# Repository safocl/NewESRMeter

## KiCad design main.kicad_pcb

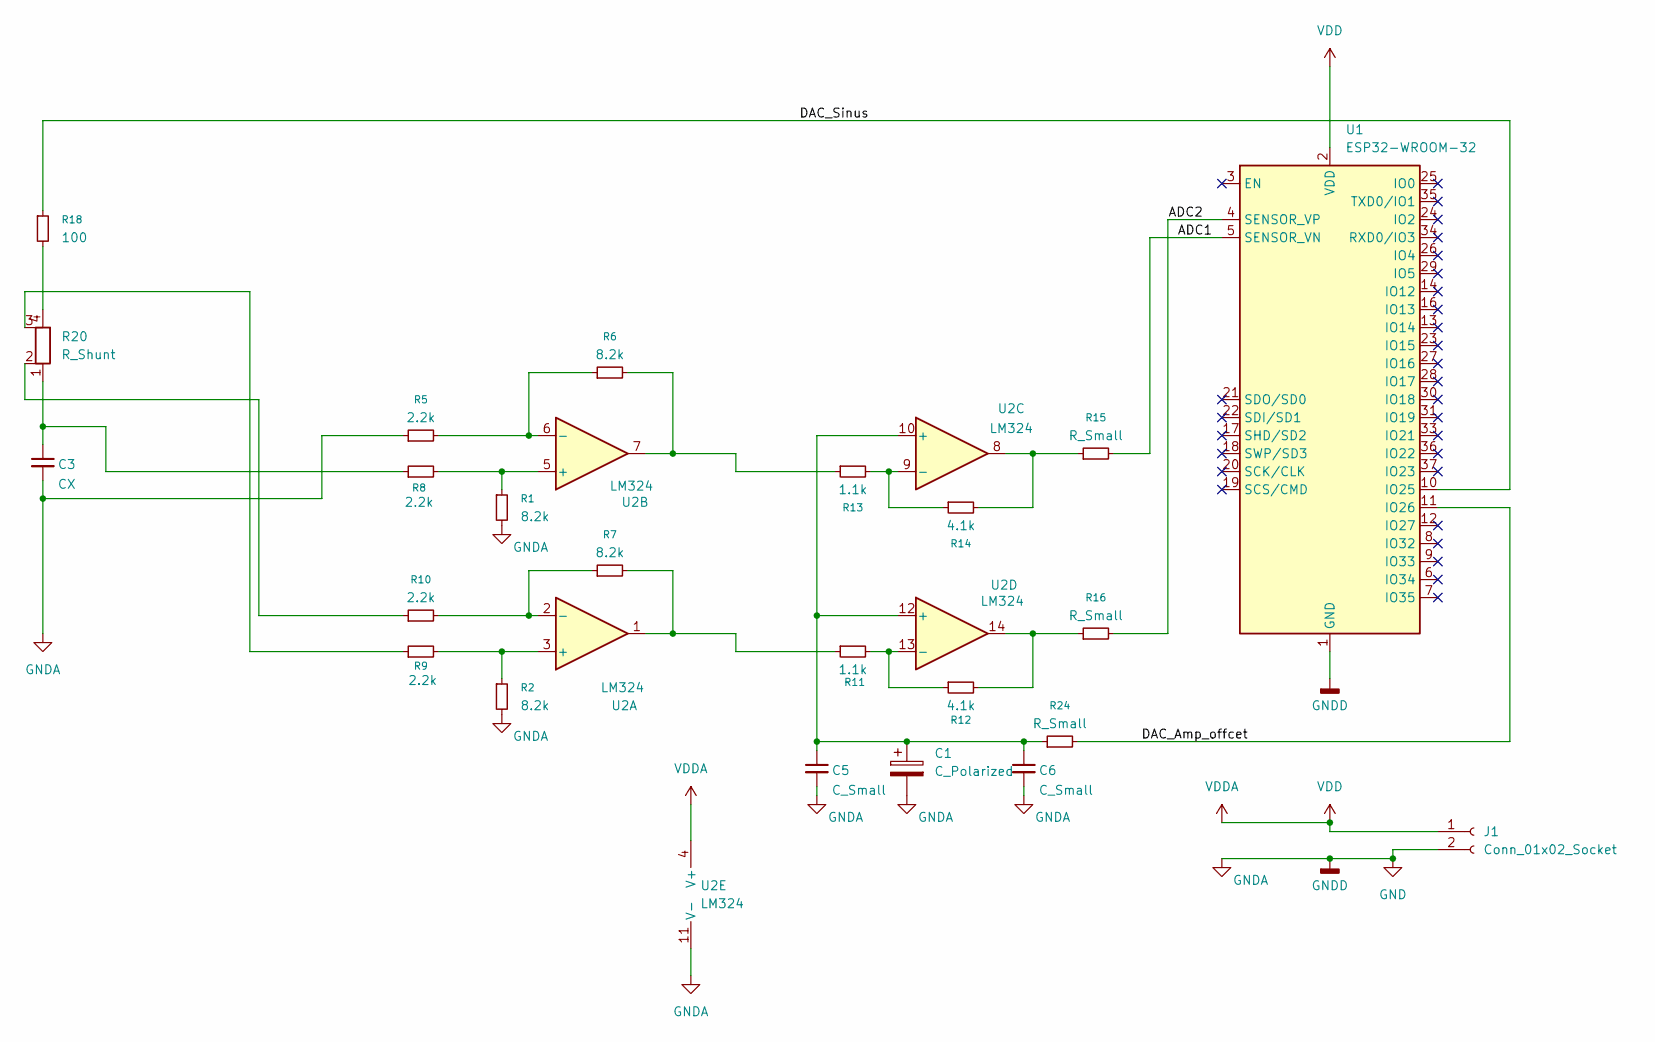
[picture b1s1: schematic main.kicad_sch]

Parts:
C1: C_Polarized; CP_Elec_3x5.3
C3: CX; C_1808_4520Metric
C5, C6: C_Small; C_0603_1608Metric
J1: Conn_01x02_Socket; AMASS_XT60-F_1x02_P7.20mm_Vertical
R1, R2, R6, R7: 8.2k; R_0603_1608Metric
R5, R8, R9, R10: 2.2k; R_0603_1608Metric
R11, R13: 1.1k; R_0603_1608Metric
R12, R14: 4.1k; R_0603_1608Metric
R15, R16, R24: R_Small; R_0603_1608Metric
R18: 100; R_0603_1608Metric
R20: R_Shunt; R_Shunt_Vishay_WSKW0612
U1: ESP32-WROOM-32
U2: LM324; SOIC-14_3.9x8.7mm_P1.27mm

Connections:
/ADC1: R15.2, U1.5 (SENSOR_VN)
/ADC2: R16.2, U1.4 (SENSOR_VP)
/DAC_Amp_offcet: R24.2, U1.11 (IO26)
/DAC_Sinus: R18.1, U1.10 (IO25)
GND: C1.2, C3.2, C5.2, C6.2, J1.2, R1.2, R2.2, R5.1, U1.1 (GND), U1.15 (GND), U1.38 (GND), U1.39 (GND), U2.11 (V-)
unnamed: C3.1, R8.1, R20.1
unnamed: R10.1, R20.2
unnamed: R7.2, R11.1, U2.1
unnamed: R12.2, R16.1, U2.14
unnamed: R6.2, R13.1, U2.7
unnamed: R14.2, R15.1, U2.8
unnamed: R18.2, R20.4
unnamed: R9.1, R20.3
unnamed: R2.1, R9.2, U2.3 (+)
unnamed: R7.1, R10.2, U2.2 (-)
unnamed: R1.1, R8.2, U2.5 (+)
unnamed: R5.2, R6.1, U2.6 (-)
unnamed: C1.1, C5.1, C6.1, R24.1, U2.10 (+), U2.12 (+)
unnamed: R13.2, R14.1, U2.9 (-)
unnamed: R11.2, R12.1, U2.13 (-)
VDD: J1.1, U1.2 (VDD), U2.4 (V+)

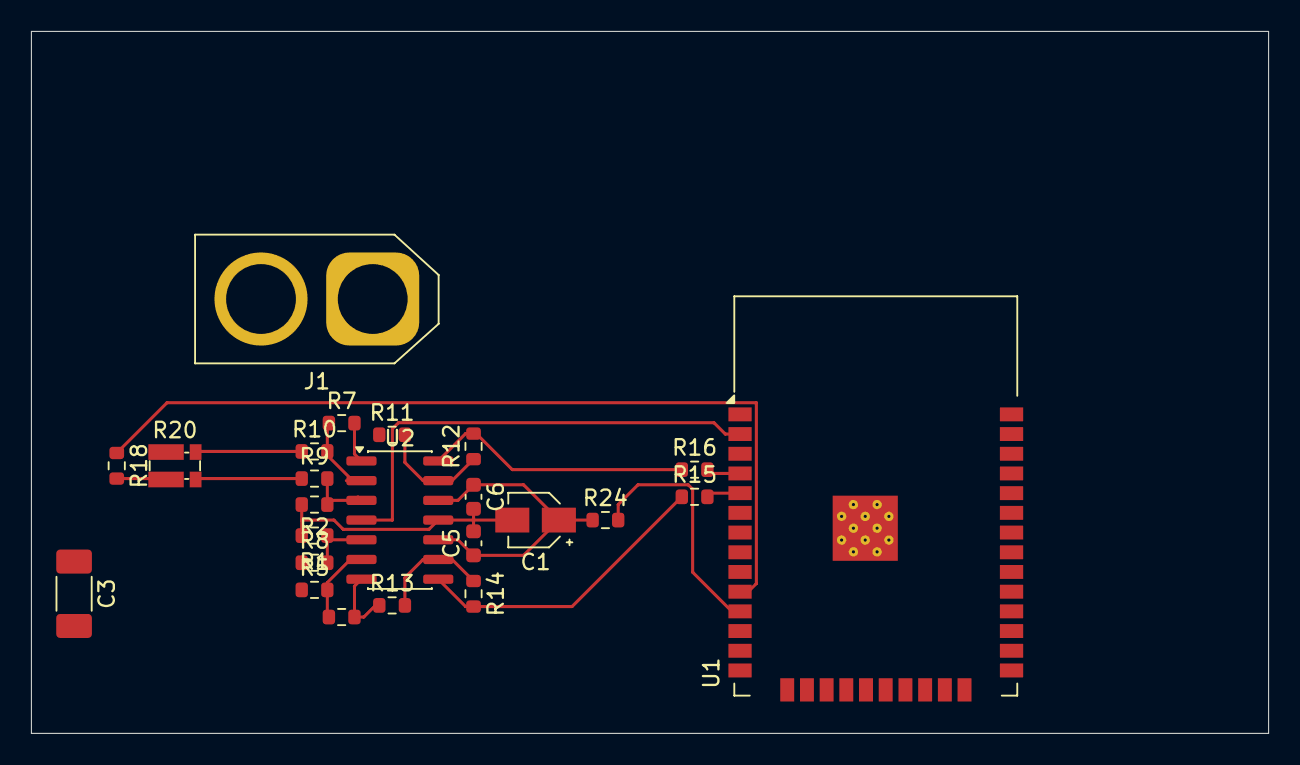
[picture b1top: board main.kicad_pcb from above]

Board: 2 copper layers, 79.8 x 45.2 mm, 24 parts (0 on the bottom side), 21 nets.
